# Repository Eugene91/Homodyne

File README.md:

# Optical Homodyne detector
The design is done with Kicad 6.0 and is based on the [Optics Communications, 285(24), 5259-5267](https://www.sciencedirect.com/science/article/abs/pii/S0030401812008255).
## Few details
- The detector is designed for [First Sensor PS1.0-6B Photodetectors](https://www.mouser.ca/datasheet/2/313/PS1.0-6b_TO_501429-586466.pdf) photodiodes, but may also work with [Hamamatsu S5972](https://www.hamamatsu.com/eu/en/product/type/S5972/index.html).
- The detector is power by ± 15 Volts that are spitted on 4 Voltage variable regulators LM337 and LM317. 
- Two regulators are used to power the 4.7 kOhm transimpedance that is based on OPA 847 with effective bandwidth 3 dB of 100 MHz
- Two reversely biased photodiodes are separately biased my other two voltage regulators.
- Compensation capacitor C18 is used to prevent oscillations of the OPA847 and is in situ adjusted within a range of 1-4pF.

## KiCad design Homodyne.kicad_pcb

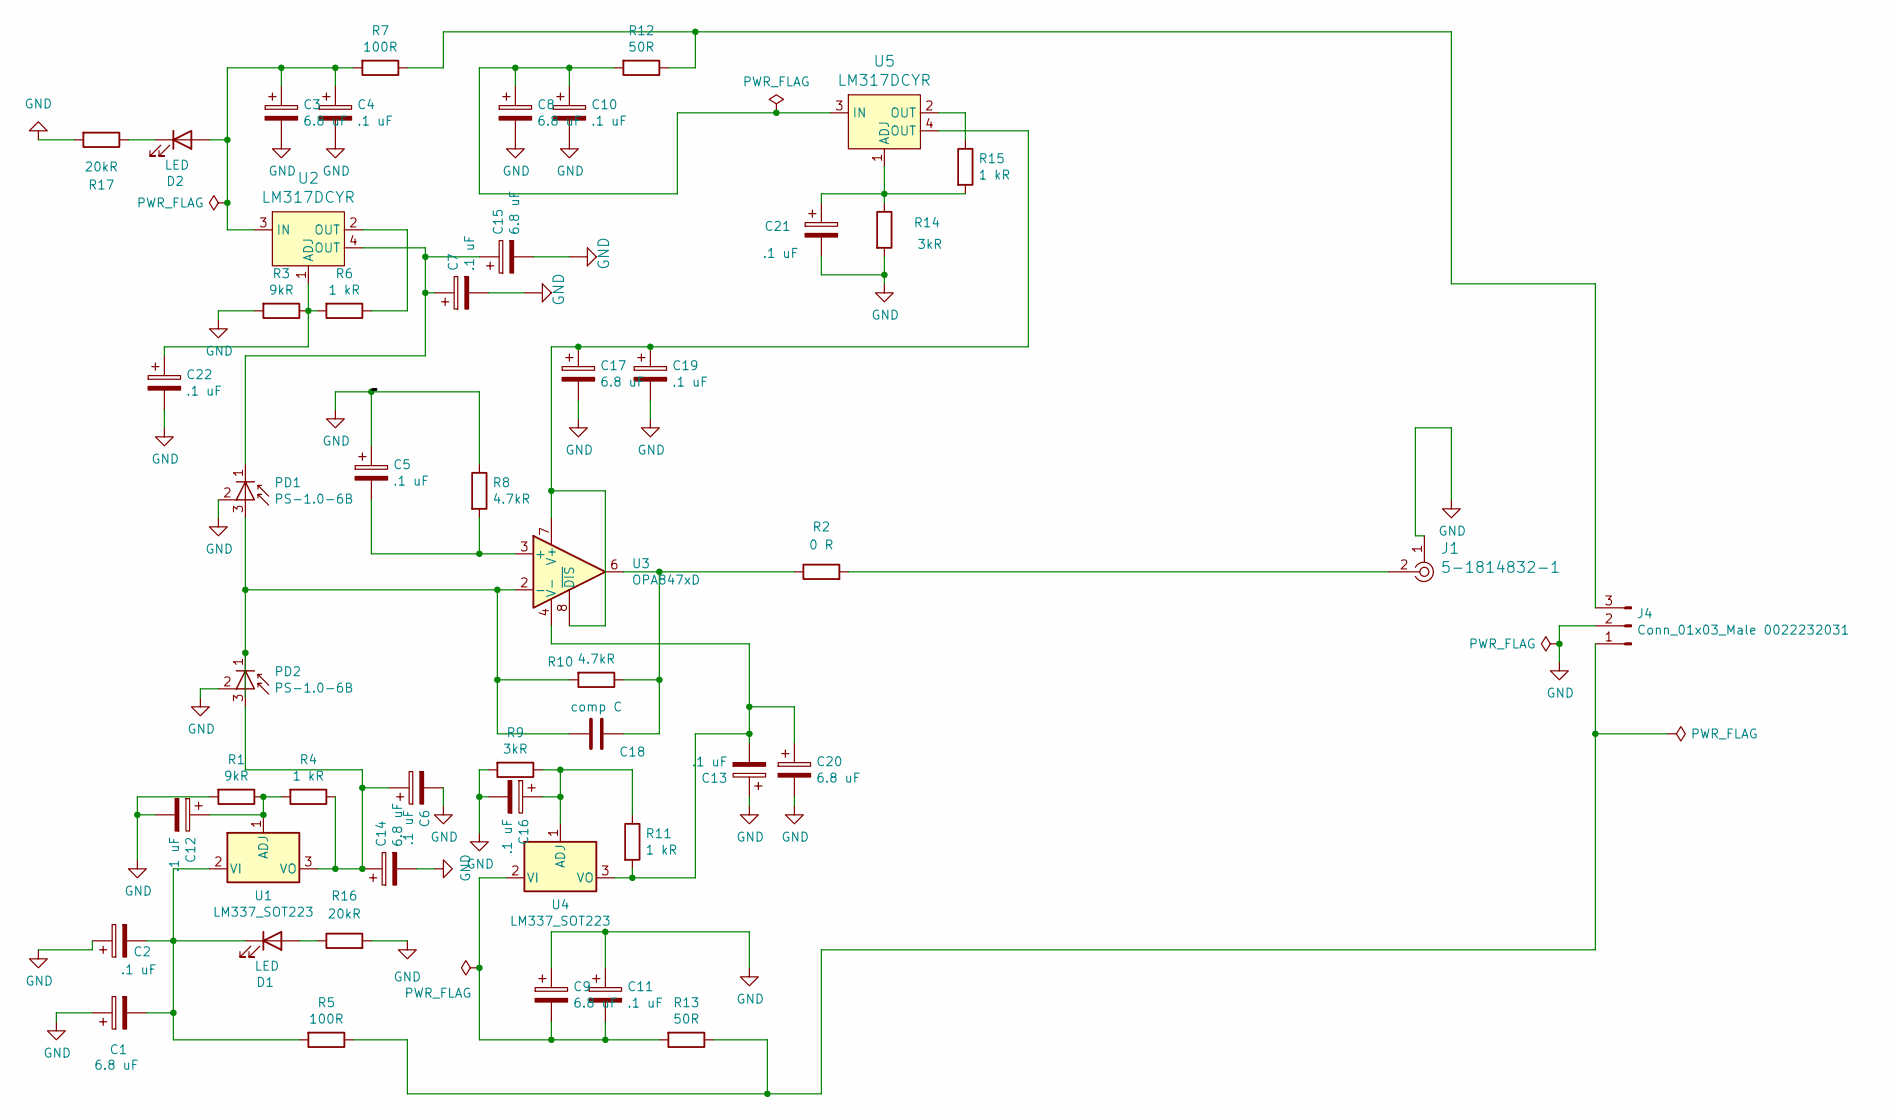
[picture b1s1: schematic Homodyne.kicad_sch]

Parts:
C1, C3, C8, C9, C14, C15, C17, C20: 6.8 uF; C_1206
C2, C4, C5, C6, C7, C10, C11, C12, C13, C16, C19, C21, C22: .1 uF; C_1206
C18: comp C; C_0603
D1, D2: LED; LED_1206_3216Metric
J1: 5-1814832-1; RF_SMA_Vertical_5-1814832-1; MPN 5-1814832-1; Digi-Key_PN A97594-ND
J4: Conn_01x03_Male 0022232031; PinHeader_1x03_P2.54mm_Vertical
PD1, PD2: PS-1.0-6B; TO-52-3
R1, R3: 9kR; R_1206_3216Metric
R2: 0 R; R_1206_3216Metric
R4, R6, R11, R15: 1 kR; R_1206_3216Metric
R5, R7: 100R; R_1206_3216Metric
R8, R10: 4.7kR; R_1206_3216Metric
R9, R14: 3kR; R_1206_3216Metric
R12, R13: 50R; R_1206_3216Metric
R16, R17: 20kR; R_1206_3216Metric
U1, U4: LM337_SOT223; SOT-223-3_TabPin2
U2, U5: LM317DCYR; SOT-223; MPN LM317DCYR; Digi-Key_PN 296-12602-1-ND
U3: OPA847xD; SOIC-8_3.9x4.9mm_P1.27mm

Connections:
GND: C1.1, C2.1, C3.2, C4.2, C5.1, C6.2, C7.2, C8.2, C9.1, C10.2, C11.1, C12.2, C13.1, C14.2, C15.2, C16.2, C17.2, C19.2, C20.2, C21.2, C22.2, J1.1, J4.2, PD1.2 (CASE), PD2.2 (CASE), R1.2, R3.2, R8.1, R9.2, R14.2, R16.2, R17.2
unnamed: C18.1, R2.1, R10.1, U3.6
unnamed: D1.2 (A), R16.1
unnamed: C1.2, C2.2, D1.1 (K), R5.2, U1.2 (VI)
unnamed: C3.1, C4.1, D2.2 (A), R7.2, U2.3 (IN)
unnamed: D2.1 (K), R17.1
unnamed: J1.2, R2.2
unnamed: J4.1, R5.1, R13.1
unnamed: J4.3, R7.1, R12.1
unnamed: C18.2, PD1.3 (A), PD2.1 (K), R10.2, U3.2 (-)
unnamed: C7.1, C15.1, PD1.1 (K), U2.4 (OUT)
unnamed: C6.1, C14.1, PD2.3 (A), R4.1, U1.3 (VO)
unnamed: R6.1, U2.2 (OUT)
unnamed: R15.1, U5.2 (OUT)
unnamed: C12.1, R1.1, R4.2, U1.1 (ADJ)
unnamed: C22.1, R3.1, R6.2, U2.1 (ADJ)
unnamed: C5.2, R8.2, U3.3 (+)
unnamed: C17.1, C19.1, U3.7 (V+), U3.8 (~DIS), U5.4 (OUT)
unnamed: C13.2, C20.1, R11.2, U3.4 (V-), U4.3 (VO)
unnamed: C16.1, R9.1, R11.1, U4.1 (ADJ)
unnamed: C9.2, C11.2, R13.2, U4.2 (VI)
unnamed: C21.1, R14.1, R15.2, U5.1 (ADJ)
unnamed: C8.1, C10.1, R12.2, U5.3 (IN)

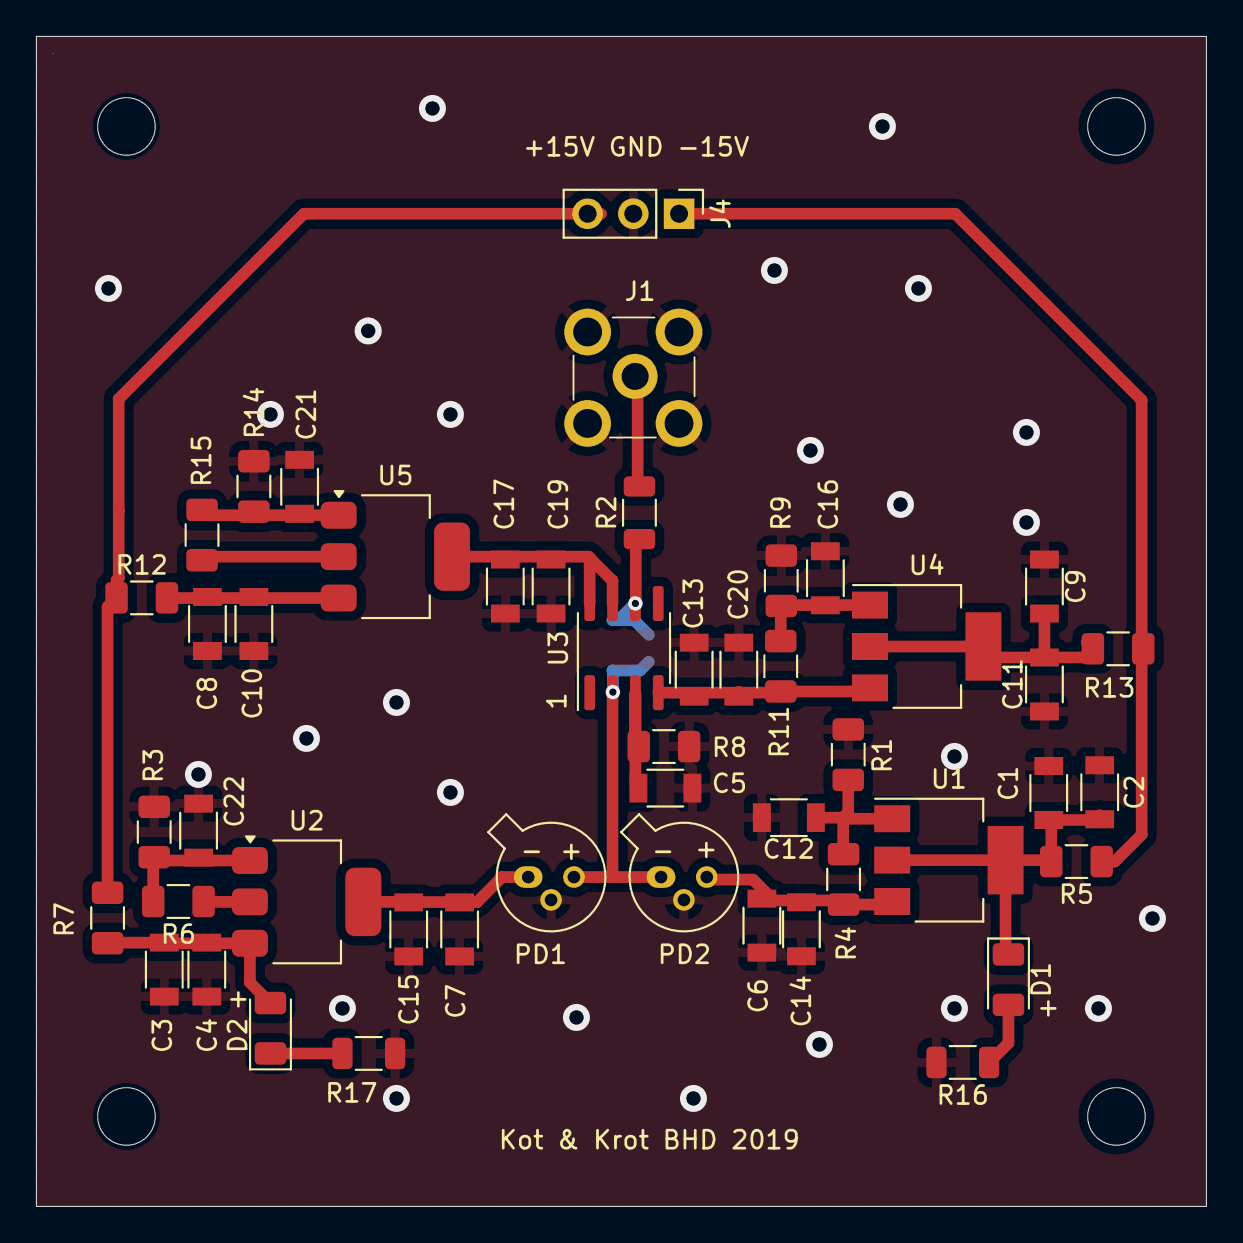
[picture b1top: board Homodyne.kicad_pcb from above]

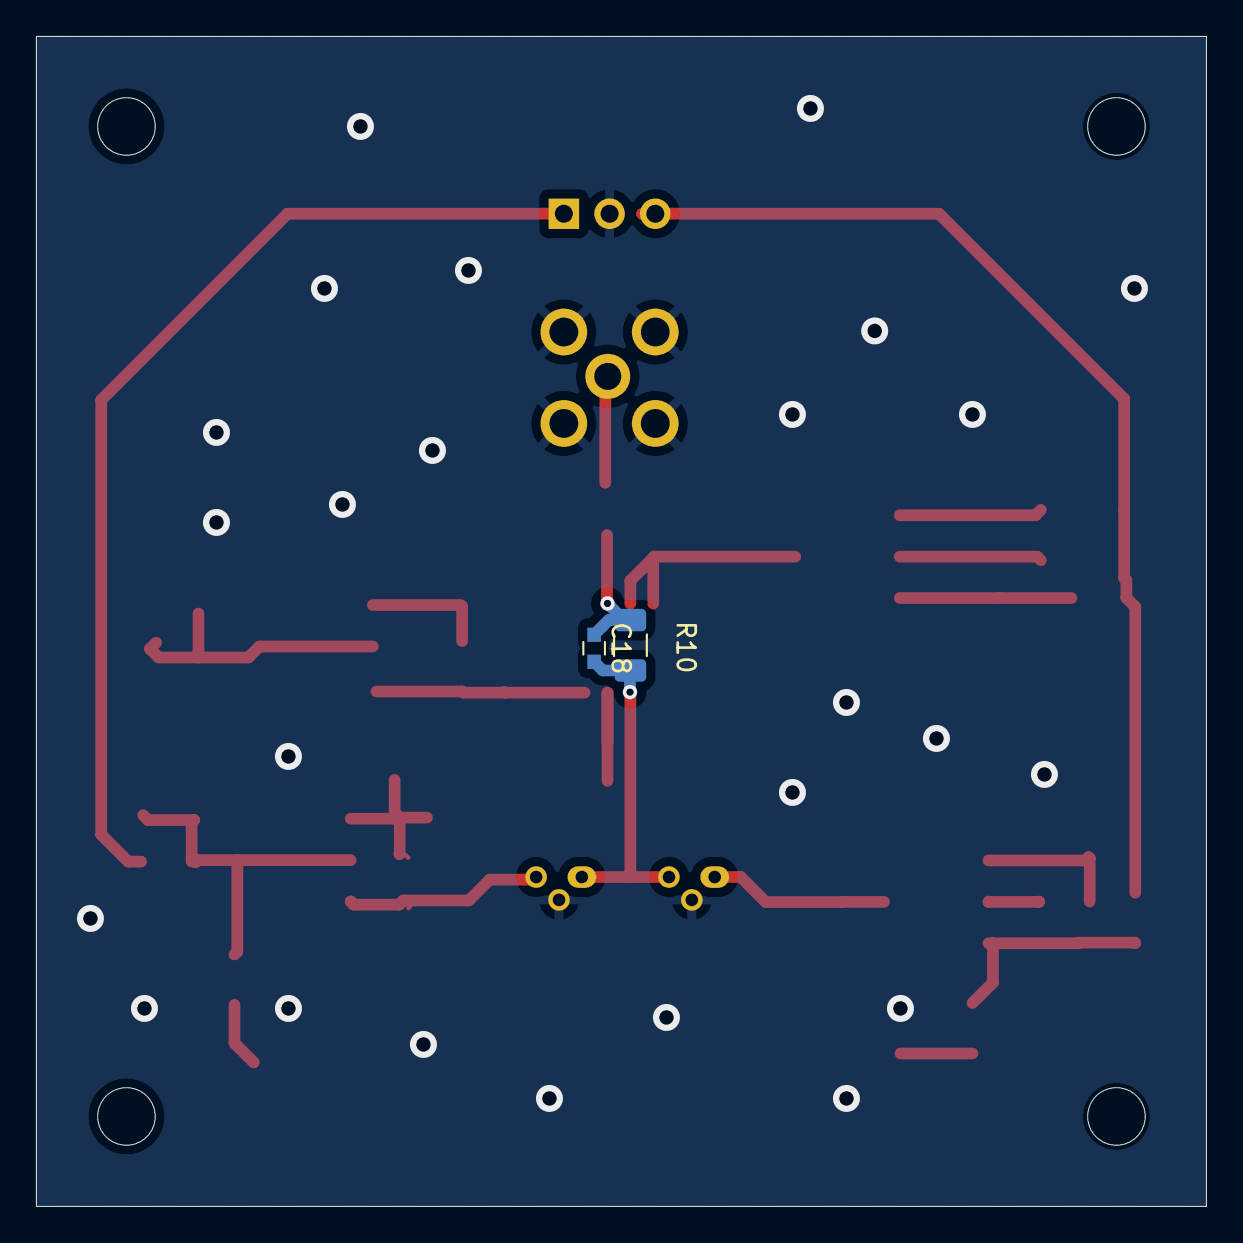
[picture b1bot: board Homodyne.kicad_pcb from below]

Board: 2 copper layers, 65.0 x 65.0 mm, 50 parts (2 on the bottom side), 23 nets.

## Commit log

2023-01-23 v 0.1
2023-01-24 Small fix
2024-07-06 Updated the board size to 65x65 mm
